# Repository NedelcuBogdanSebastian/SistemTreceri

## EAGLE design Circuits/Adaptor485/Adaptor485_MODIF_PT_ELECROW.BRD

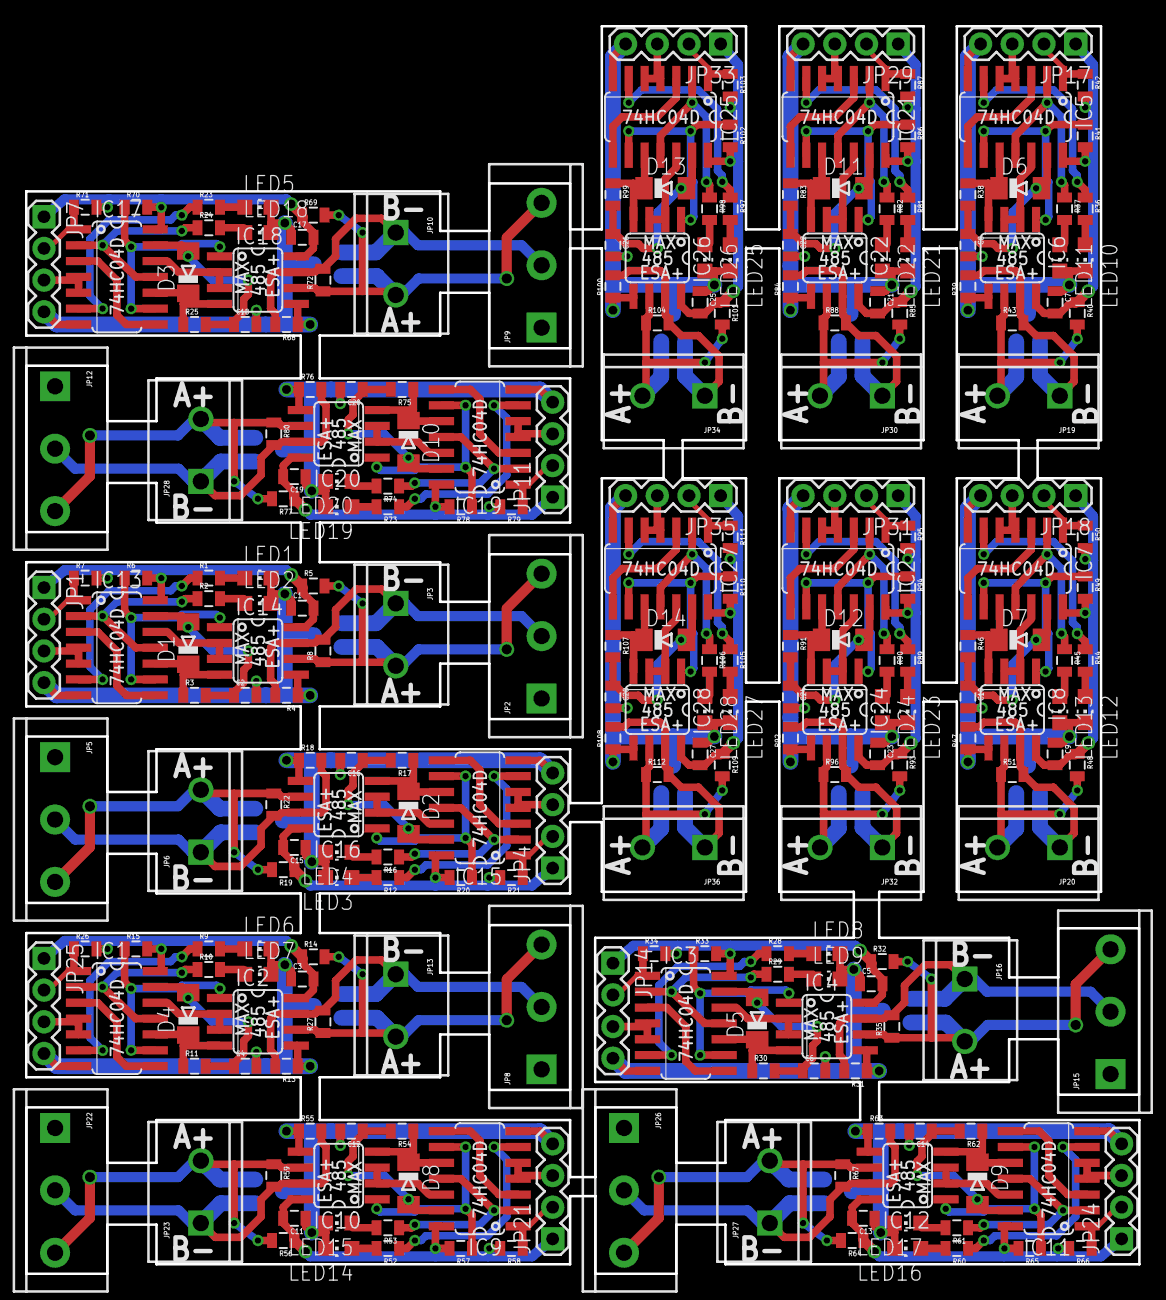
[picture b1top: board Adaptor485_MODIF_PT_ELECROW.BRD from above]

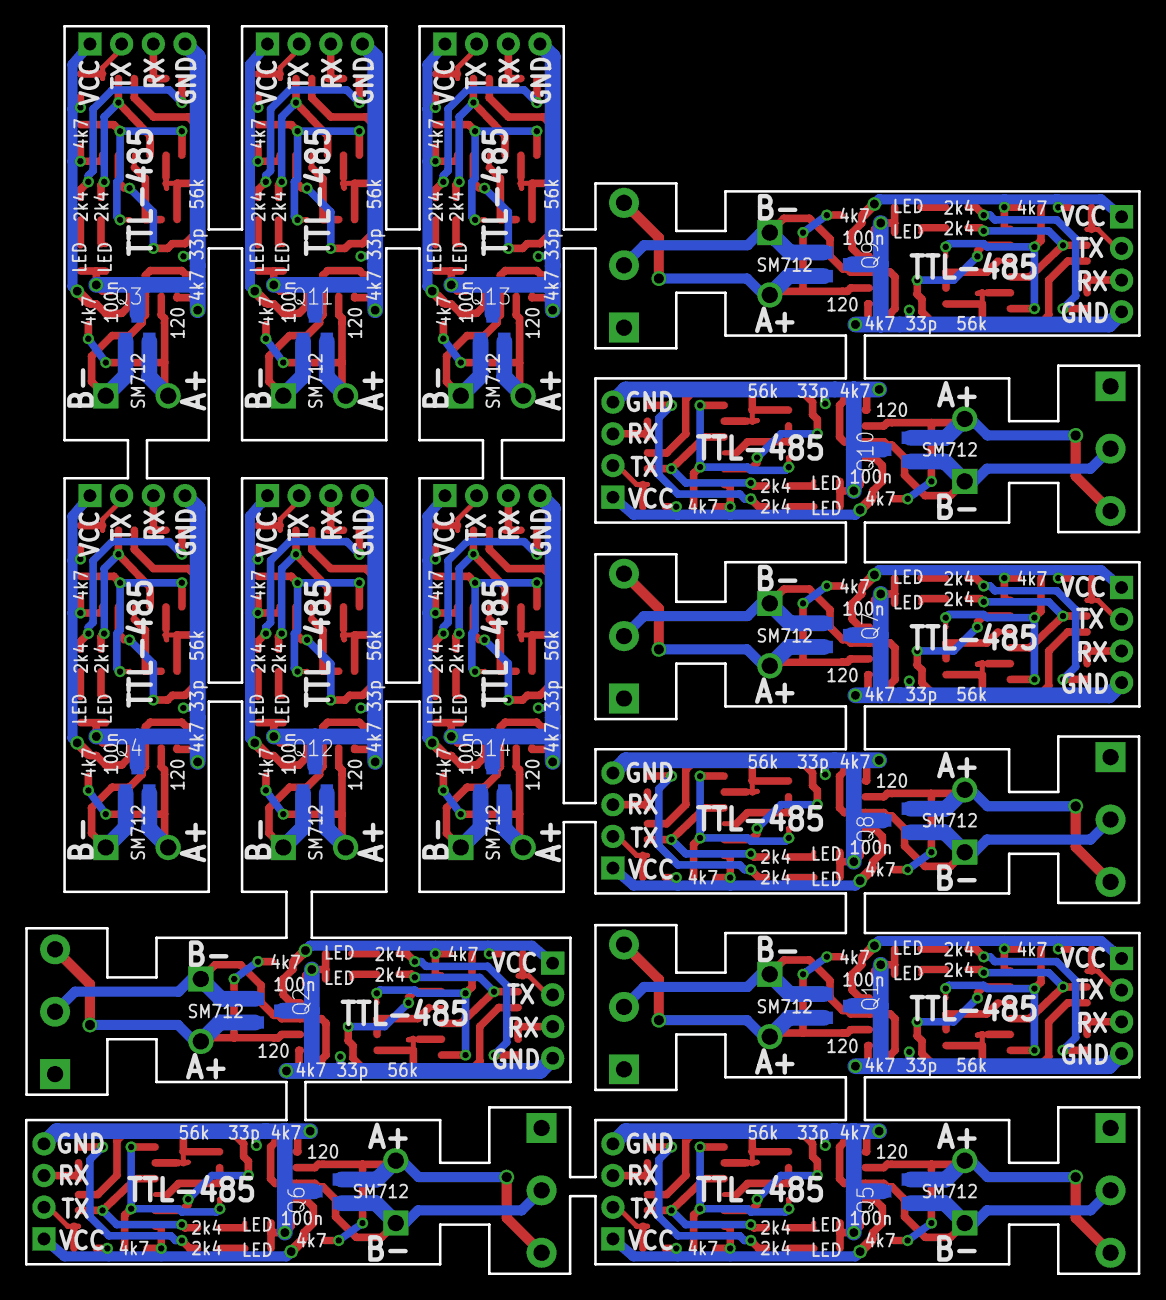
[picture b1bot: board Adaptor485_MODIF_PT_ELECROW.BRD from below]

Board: 2 copper layers, 89.2 x 100.0 mm, 260 parts (14 on the bottom side), 210 nets.

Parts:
C1, C3, C5, C7, C9, C11, C13, C15, C17, C19, C21, C23, C25, C27: 100n; 0805
C2, C4, C6, C8, C10, C12, C14, C16, C18, C20, C22, C24, C26, C28: 33pF; 0805
D1, D2, D3, D4, D5, D6, D7, D8, D9, D10, D11, D12, D13, D14: 1N4148; MINIMELF
IC1, IC3, IC5, IC7, IC9, IC11, IC13, IC15, IC17, IC19, IC21, IC23, IC25, IC27: 74HC04D; SO14
IC2, IC4, IC6, IC8, IC10, IC12, IC14, IC16, IC18, IC20, IC22, IC24, IC26, IC28: MAX3468CSA; SO08
JP1, JP4, JP7, JP11, JP14, JP17, JP18, JP21, JP24, JP25, JP29, JP31, JP33, JP35: 1X04
JP2, JP5, JP8, JP9, JP12, JP15, JP22, JP26: SCREWTERMINAL-5MM-3
JP3, JP6, JP10, JP13, JP16, JP19, JP20, JP23, JP27, JP28, JP30, JP32, JP34, JP36: SCREWTERMINAL-5MM-2
LED1, LED2, LED3, LED4, LED5, LED6, LED7, LED8, LED9, LED10, LED11, LED12, LED13, LED14, LED15, LED16, LED17, LED18, LED19, LED20, LED21, LED22, LED23, LED24, LED25, LED26, LED27, LED28: CHIP-LED0805
Q1, Q2, Q3, Q4, Q5, Q6, Q7, Q8, Q9, Q10, Q11, Q12, Q13, Q14: BCX70SMD; SOT23
R1, R2, R9, R10, R12, R16, R23, R24, R28, R29, R36, R37, R44, R45, R52, R53, R60, R61, R73, R74, R81, R82, R89, R90, R97, R98, R105, R106: 2K4; 0805
R3, R11, R17, R25, R30, R38, R46, R54, R62, R75, R83, R91, R99, R107: 56K; 0805
R4, R5, R6, R7, R13, R14, R15, R18, R19, R20, R21, R26, R31, R32, R33, R34, R39, R40, R41, R42, R47, R48, R49, R50, R55, R56, R57, R58, R63, R64, R65, R66, R68, R69, R70, R71, R76, R77, R78, R79, R84, R85, R86, R87, R92, R93, R94, R95, R100, R101, R102, R103, R108, R109, R110, R111: 4K7; 0805
R8, R22, R27, R35, R43, R51, R59, R67, R72, R80, R88, R96, R104, R112: 120; 0805

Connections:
3.3V1: C5.2, IC3.14, IC4.8, JP14.1, R32.1, R33.2, R34.2
3.3V2: C7.2, IC5.14, IC6.8, JP17.1, R40.1, R41.2, R42.2
3.3V3: C9.2, IC7.14, IC8.8, JP18.1, R48.1, R49.2, R50.2
3.3V4: C11.2, IC9.14, IC10.8, JP21.1, R56.1, R57.2, R58.2
3.3V5: C13.2, IC11.14, IC12.8, JP24.1, R64.1, R65.2, R66.2
3.3V6: C15.2, IC15.14, IC16.8, JP4.1, R19.1, R20.2, R21.2
3.3V7: C19.2, IC19.14, IC20.8, JP11.1, R77.1, R78.2, R79.2
3.3V8: C21.2, IC21.14, IC22.8, JP29.1, R85.1, R86.2, R87.2
3.3V9: C23.2, IC23.14, IC24.8, JP31.1, R93.1, R94.2, R95.2
3.3V10: C25.2, IC25.14, IC26.8, JP33.1, R101.1, R102.2, R103.2
3.3V11: C27.2, IC27.14, IC28.8, JP35.1, R109.1, R110.2, R111.2
A+: IC2.6, JP8.3, JP13.2, Q1.2, R14.2, R27.1
A+1: IC4.6, JP15.3, JP16.2, Q2.2, R32.2, R35.1
A+2: IC6.6, JP19.2, Q3.2, R40.2, R43.1
A+3: IC8.6, JP20.2, Q4.2, R48.2, R51.1
A+4: IC10.6, JP22.3, JP23.2, Q5.2, R56.2, R59.1
A+5: IC12.6, JP26.3, JP27.2, Q6.2, R64.2, R67.1
A+6: IC14.6, JP2.3, JP3.2, Q7.2, R5.2, R8.1
A+7: IC16.6, JP5.3, JP6.2, Q8.2, R19.2, R22.1
A+8: IC18.6, JP9.3, JP10.2, Q9.2, R69.2, R72.1
A+9: IC20.6, JP12.3, JP28.2, Q10.2, R77.2, R80.1
A+10: IC22.6, JP30.2, Q11.2, R85.2, R88.1
A+11: IC24.6, JP32.2, Q12.2, R93.2, R96.1
A+12: IC26.6, JP34.2, Q13.2, R101.2, R104.1
A+13: IC28.6, JP36.2, Q14.2, R109.2, R112.1
B-: IC2.7, JP8.2, JP13.1, Q1.1, R13.2, R27.2
B-1: IC4.7, JP15.2, JP16.1, Q2.1, R31.2, R35.2
B-2: IC6.7, JP19.1, Q3.1, R39.2, R43.2
B-3: IC8.7, JP20.1, Q4.1, R47.2, R51.2
B-4: IC10.7, JP22.2, JP23.1, Q5.1, R55.2, R59.2
B-5: IC12.7, JP26.2, JP27.1, Q6.1, R63.2, R67.2
B-6: IC14.7, JP2.2, JP3.1, Q7.1, R4.2, R8.2
B-7: IC16.7, JP5.2, JP6.1, Q8.1, R18.2, R22.2
B-8: IC18.7, JP9.2, JP10.1, Q9.1, R68.2, R72.2
B-9: IC20.7, JP12.2, JP28.1, Q10.1, R76.2, R80.2
B-10: IC22.7, JP30.1, Q11.1, R84.2, R88.2
B-11: IC24.7, JP32.1, Q12.1, R92.2, R96.2
B-12: IC26.7, JP34.1, Q13.1, R100.2, R104.2
B-13: IC28.7, JP36.1, Q14.1, R108.2, R112.2
GND: C3.1, C4.2, IC1.7, IC2.5, JP25.4, LED6.C, LED7.C, Q1.3, R13.1
GND2: C5.1, C6.2, IC3.7, IC4.5, JP14.4, LED8.C, LED9.C, Q2.3, R31.1
GND3: C7.1, C8.2, IC5.7, IC6.5, JP17.4, LED10.C, LED11.C, Q3.3, R39.1
GND4: C9.1, C10.2, IC7.7, IC8.5, JP18.4, LED12.C, LED13.C, Q4.3, R47.1
GND5: C11.1, C12.2, IC9.7, IC10.5, JP21.4, LED14.C, LED15.C, Q5.3, R55.1
GND6: C13.1, C14.2, IC11.7, IC12.5, JP24.4, LED16.C, LED17.C, Q6.3, R63.1
GND7: C1.1, C2.2, IC13.7, IC14.5, JP1.4, LED1.C, LED2.C, Q7.3, R4.1
GND8: C15.1, C16.2, IC15.7, IC16.5, JP4.4, LED3.C, LED4.C, Q8.3, R18.1
GND9: C17.1, C18.2, IC17.7, IC18.5, JP7.4, LED5.C, LED18.C, Q9.3, R68.1
GND10: C19.1, C20.2, IC19.7, IC20.5, JP11.4, LED19.C, LED20.C, Q10.3, R76.1
GND11: C21.1, C22.2, IC21.7, IC22.5, JP29.4, LED21.C, LED22.C, Q11.3, R84.1
GND12: C23.1, C24.2, IC23.7, IC24.5, JP31.4, LED23.C, LED24.C, Q12.3, R92.1
GND13: C25.1, C26.2, IC25.7, IC26.5, JP33.4, LED25.C, LED26.C, Q13.3, R100.1
GND14: C27.1, C28.2, IC27.7, IC28.5, JP35.4, LED27.C, LED28.C, Q14.3, R108.1
unnamed: IC13.9, IC14.1, R6.1
unnamed: IC13.3, IC13.8
unnamed: C2.1, D1.A, IC13.13, R3.2
unnamed: IC13.6, R1.1
unnamed: D1.C, IC13.10, IC14.4, R3.1
unnamed: IC13.12, IC14.2, IC14.3
unnamed: LED2.A, R2.2
unnamed: LED1.A, R1.2
unnamed: IC13.2, IC13.11, R2.1
unnamed: IC15.9, IC16.1, R20.1
unnamed: IC15.3, IC15.8
unnamed: C16.1, D2.A, IC15.13, R17.2
unnamed: IC3.9, IC4.1, R33.1
unnamed: IC3.3, IC3.8
unnamed: C6.1, D5.A, IC3.13, R30.2
unnamed: LED7.A, R10.2
unnamed: LED6.A, R9.2
unnamed: IC3.6, R28.1
unnamed: IC1.2, IC1.11, R10.1
unnamed: D5.C, IC3.10, IC4.4, R30.1
unnamed: IC1.9, IC2.1, R15.1
unnamed: IC15.6, R12.1
unnamed: IC1.3, IC1.8
unnamed: C4.1, D4.A, IC1.13, R11.2
unnamed: IC3.12, IC4.2, IC4.3
unnamed: LED9.A, R29.2
unnamed: IC1.6, R9.1
unnamed: LED8.A, R28.2
unnamed: D4.C, IC1.10, IC2.4, R11.1
unnamed: IC1.12, IC2.2, IC2.3
unnamed: IC3.2, IC3.11, R29.1
unnamed: IC5.9, IC6.1, R41.1
unnamed: IC5.3, IC5.8
unnamed: C8.1, D6.A, IC5.13, R38.2
unnamed: IC5.6, R36.1
unnamed: D6.C, IC5.10, IC6.4, R38.1
unnamed: IC5.12, IC6.2, IC6.3
unnamed: LED11.A, R37.2
unnamed: LED10.A, R36.2
unnamed: IC5.2, IC5.11, R37.1
unnamed: IC7.9, IC8.1, R49.1
unnamed: IC7.3, IC7.8
unnamed: C10.1, D7.A, IC7.13, R46.2
unnamed: IC7.6, R44.1
unnamed: D7.C, IC7.10, IC8.4, R46.1
unnamed: IC7.12, IC8.2, IC8.3
unnamed: LED13.A, R45.2
unnamed: LED12.A, R44.2
unnamed: IC7.2, IC7.11, R45.1
unnamed: IC9.9, IC10.1, R57.1
unnamed: IC9.3, IC9.8
unnamed: C12.1, D8.A, IC9.13, R54.2
unnamed: D2.C, IC15.10, IC16.4, R17.1
unnamed: IC15.12, IC16.2, IC16.3
unnamed: LED4.A, R16.2
unnamed: LED3.A, R12.2
unnamed: IC15.2, IC15.11, R16.1
unnamed: IC17.9, IC18.1, R70.1
unnamed: IC17.3, IC17.8
unnamed: C18.1, D3.A, IC17.13, R25.2
unnamed: IC17.6, R23.1
unnamed: D3.C, IC17.10, IC18.4, R25.1
unnamed: IC9.6, R52.1
unnamed: D8.C, IC9.10, IC10.4, R54.1
unnamed: IC9.12, IC10.2, IC10.3
unnamed: LED15.A, R53.2
unnamed: LED14.A, R52.2
unnamed: IC9.2, IC9.11, R53.1
unnamed: IC11.9, IC12.1, R65.1
unnamed: IC11.3, IC11.8
unnamed: C14.1, D9.A, IC11.13, R62.2
unnamed: IC11.6, R60.1
unnamed: D9.C, IC11.10, IC12.4, R62.1
unnamed: IC11.12, IC12.2, IC12.3
unnamed: LED17.A, R61.2
unnamed: LED16.A, R60.2
unnamed: IC17.12, IC18.2, IC18.3
unnamed: LED18.A, R24.2
unnamed: IC11.2, IC11.11, R61.1
unnamed: LED5.A, R23.2
unnamed: IC17.2, IC17.11, R24.1
unnamed: IC19.9, IC20.1, R78.1
unnamed: IC19.3, IC19.8
unnamed: C20.1, D10.A, IC19.13, R75.2
unnamed: IC19.6, R73.1
unnamed: D10.C, IC19.10, IC20.4, R75.1
unnamed: IC19.12, IC20.2, IC20.3
unnamed: LED20.A, R74.2
unnamed: LED19.A, R73.2
unnamed: IC19.2, IC19.11, R74.1
unnamed: IC21.9, IC22.1, R86.1
unnamed: IC21.3, IC21.8
unnamed: C22.1, D11.A, IC21.13, R83.2
unnamed: IC21.6, R81.1
unnamed: D11.C, IC21.10, IC22.4, R83.1
unnamed: IC21.12, IC22.2, IC22.3
unnamed: LED22.A, R82.2
unnamed: LED21.A, R81.2
unnamed: IC21.2, IC21.11, R82.1
unnamed: IC23.9, IC24.1, R94.1
unnamed: IC23.3, IC23.8
unnamed: C24.1, D12.A, IC23.13, R91.2
unnamed: IC23.6, R89.1
unnamed: D12.C, IC23.10, IC24.4, R91.1
unnamed: IC23.12, IC24.2, IC24.3
unnamed: LED24.A, R90.2
unnamed: LED23.A, R89.2
unnamed: IC23.2, IC23.11, R90.1
unnamed: IC25.9, IC26.1, R102.1
unnamed: IC25.3, IC25.8
unnamed: C26.1, D13.A, IC25.13, R99.2
unnamed: IC25.6, R97.1
unnamed: D13.C, IC25.10, IC26.4, R99.1
unnamed: IC25.12, IC26.2, IC26.3
unnamed: LED26.A, R98.2
unnamed: LED25.A, R97.2
unnamed: IC25.2, IC25.11, R98.1
unnamed: IC27.9, IC28.1, R110.1
unnamed: IC27.3, IC27.8
unnamed: C28.1, D14.A, IC27.13, R107.2
unnamed: IC27.6, R105.1
unnamed: D14.C, IC27.10, IC28.4, R107.1
unnamed: IC27.12, IC28.2, IC28.3
unnamed: LED28.A, R106.2
unnamed: LED27.A, R105.2
unnamed: IC27.2, IC27.11, R106.1
RX: IC1.1, JP25.2, R26.1
RX1: IC3.1, JP14.2, R34.1
RX2: IC5.1, JP17.2, R42.1
RX3: IC7.1, JP18.2, R50.1
RX4: IC9.1, JP21.2, R58.1
RX5: IC11.1, JP24.2, R66.1
RX6: IC13.1, JP1.2, R7.1
RX7: IC15.1, JP4.2, R21.1
RX8: IC17.1, JP7.2, R71.1
RX9: IC19.1, JP11.2, R79.1
RX10: IC21.1, JP29.2, R87.1
RX11: IC23.1, JP31.2, R95.1
RX12: IC25.1, JP33.2, R103.1
RX13: IC27.1, JP35.2, R111.1
S$1: C3.2, IC1.14, IC2.8, JP25.1, R14.1, R15.2, R26.2
S$2: C1.2, IC13.14, IC14.8, JP1.1, R5.1, R6.2, R7.2
S$3: C17.2, IC17.14, IC18.8, JP7.1, R69.1, R70.2, R71.2
TX: IC1.4, IC1.5, JP25.3
TX1: IC3.4, IC3.5, JP14.3
TX2: IC5.4, IC5.5, JP17.3
TX3: IC7.4, IC7.5, JP18.3
TX4: IC9.4, IC9.5, JP21.3
TX5: IC11.4, IC11.5, JP24.3
TX6: IC13.4, IC13.5, JP1.3
TX7: IC15.4, IC15.5, JP4.3
TX8: IC17.4, IC17.5, JP7.3
TX9: IC19.4, IC19.5, JP11.3
TX10: IC21.4, IC21.5, JP29.3
TX11: IC23.4, IC23.5, JP31.3
TX12: IC25.4, IC25.5, JP33.3
TX13: IC27.4, IC27.5, JP35.3

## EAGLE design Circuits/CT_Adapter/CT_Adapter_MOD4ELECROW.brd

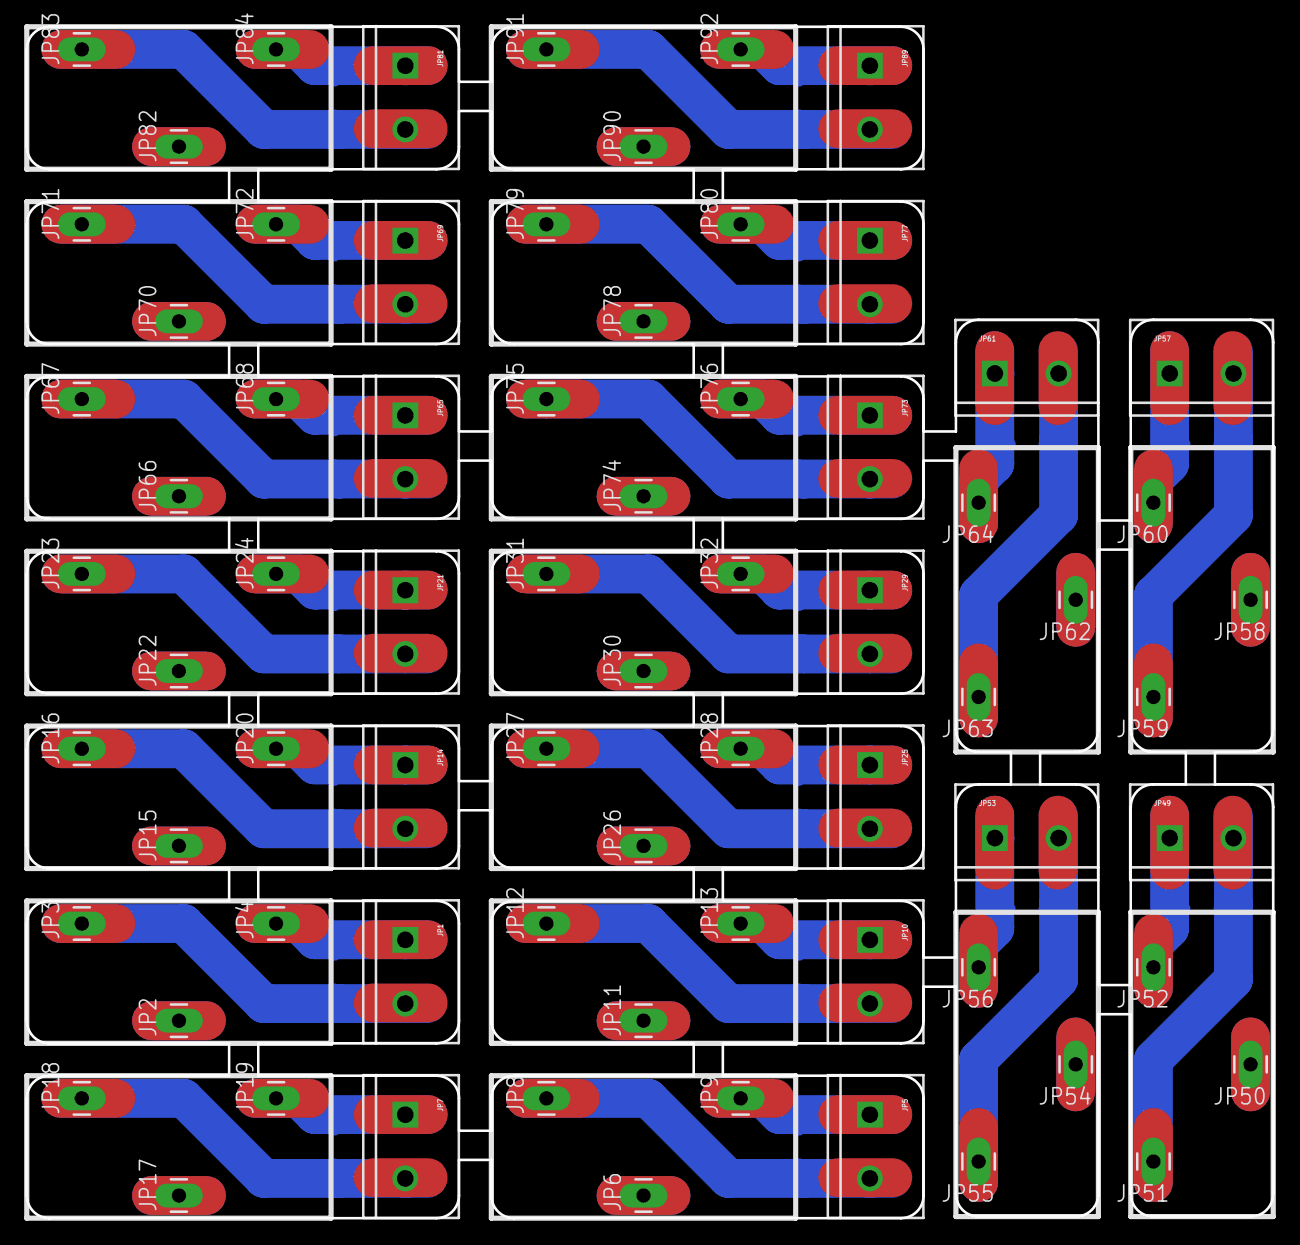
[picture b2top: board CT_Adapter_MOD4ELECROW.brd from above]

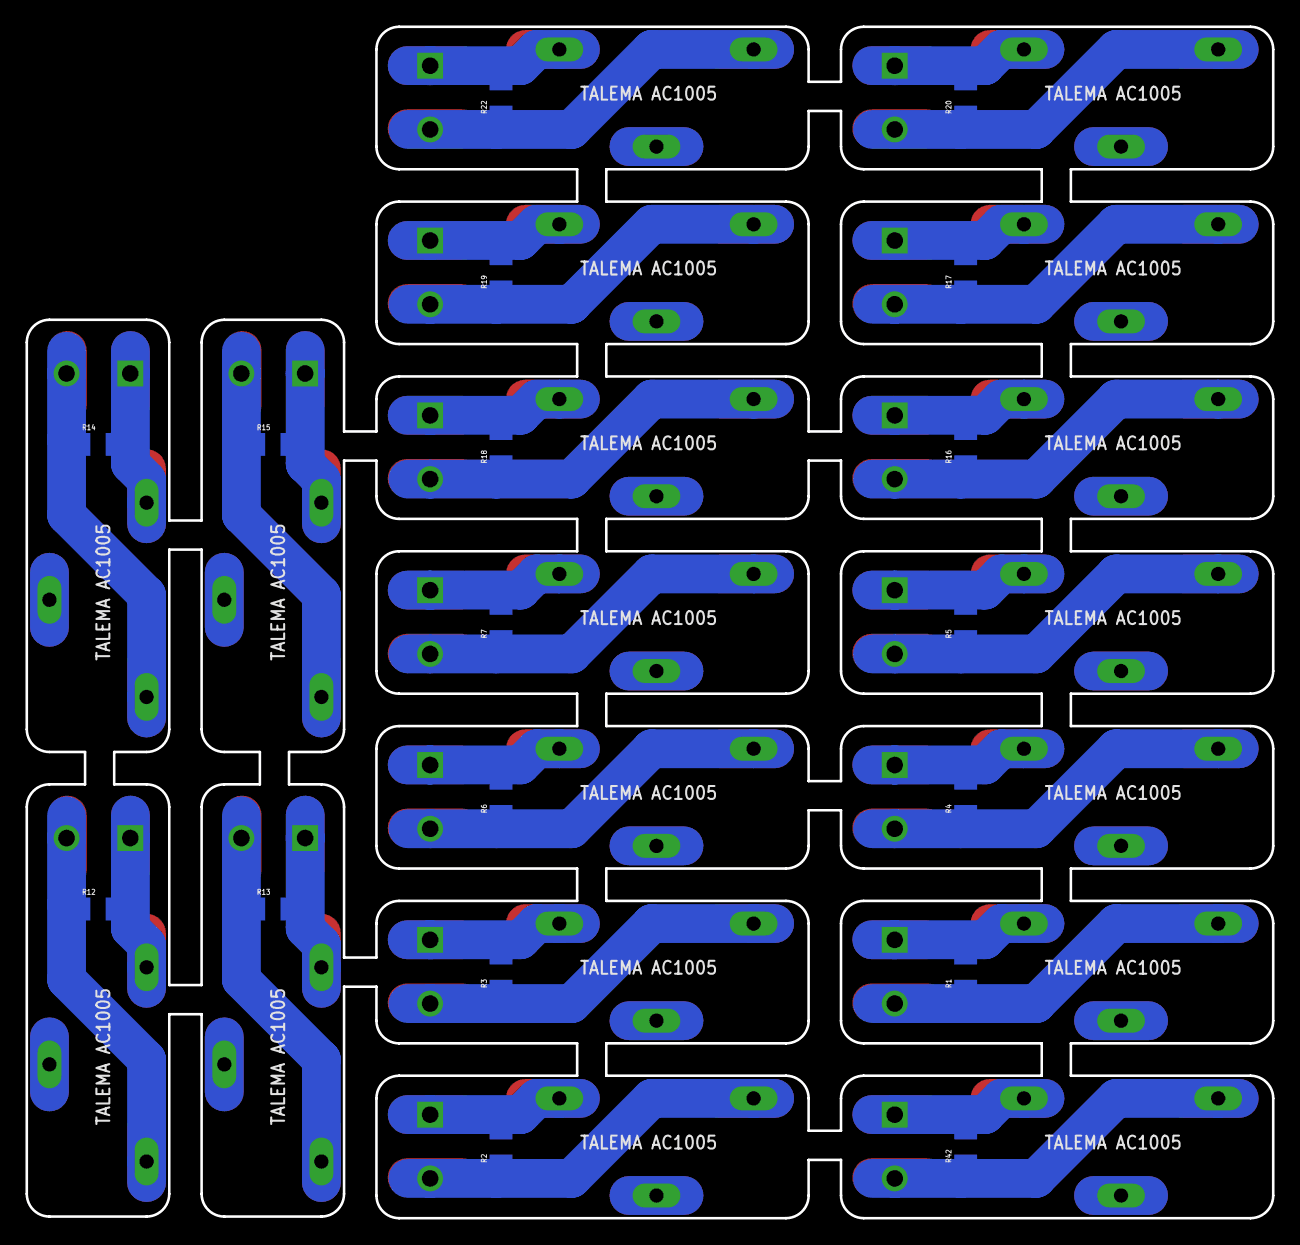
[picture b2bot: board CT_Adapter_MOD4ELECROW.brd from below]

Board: 2 copper layers, 97.8 x 93.5 mm, 90 parts (18 on the bottom side), 36 nets.

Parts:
JP1, JP5, JP7, JP10, JP14, JP21, JP25, JP29, JP49, JP53, JP57, JP61, JP65, JP69, JP73, JP77, JP81, JP89: SCREWTERMINAL-5MM-2
JP2, JP3, JP4, JP6, JP8, JP9, JP11, JP12, JP13, JP15, JP16, JP17, JP18, JP19, JP20, JP22, JP23, JP24, JP26, JP27, JP28, JP30, JP31, JP32, JP50, JP51, JP52, JP54, JP55, JP56, JP58, JP59, JP60, JP62, JP63, JP64, JP66, JP67, JP68, JP70, JP71, JP72, JP74, JP75, JP76, JP78, JP79, JP80, JP82, JP83, JP84, JP90, JP91, JP92: 1X01_LONGPAD
R1, R2, R3, R4, R5, R6, R7, R12, R13, R14, R15, R16, R17, R18, R19, R20, R22, R42: 50ohm; 1206

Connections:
AGND: JP7.1, JP19.1, R42.2
AGND1: JP1.1, JP4.1, R1.2
AGND2: JP5.1, JP9.1, R2.2
AGND3: JP10.1, JP13.1, R3.2
AGND4: JP14.1, JP20.1, R4.2
AGND5: JP21.1, JP24.1, R5.2
AGND6: JP25.1, JP28.1, R6.2
AGND7: JP29.1, JP32.1, R7.2
AGND12: JP49.1, JP52.1, R12.2
AGND13: JP53.1, JP56.1, R13.2
AGND14: JP57.1, JP60.1, R14.2
AGND15: JP61.1, JP64.1, R15.2
AGND16: JP65.1, JP68.1, R16.2
AGND17: JP69.1, JP72.1, R17.2
AGND18: JP73.1, JP76.1, R18.2
AGND19: JP77.1, JP80.1, R19.2
AGND20: JP81.1, JP84.1, R20.2
AGND22: JP89.1, JP92.1, R22.2
unnamed: JP7.2, JP18.1, R42.1
unnamed: JP1.2, JP3.1, R1.1
unnamed: JP5.2, JP8.1, R2.1
unnamed: JP10.2, JP12.1, R3.1
unnamed: JP14.2, JP16.1, R4.1
unnamed: JP21.2, JP23.1, R5.1
unnamed: JP25.2, JP27.1, R6.1
unnamed: JP29.2, JP31.1, R7.1
unnamed: JP49.2, JP51.1, R12.1
unnamed: JP53.2, JP55.1, R13.1
unnamed: JP57.2, JP59.1, R14.1
unnamed: JP61.2, JP63.1, R15.1
unnamed: JP65.2, JP67.1, R16.1
unnamed: JP69.2, JP71.1, R17.1
unnamed: JP73.2, JP75.1, R18.1
unnamed: JP77.2, JP79.1, R19.1
unnamed: JP81.2, JP83.1, R20.1
unnamed: JP89.2, JP91.1, R22.1

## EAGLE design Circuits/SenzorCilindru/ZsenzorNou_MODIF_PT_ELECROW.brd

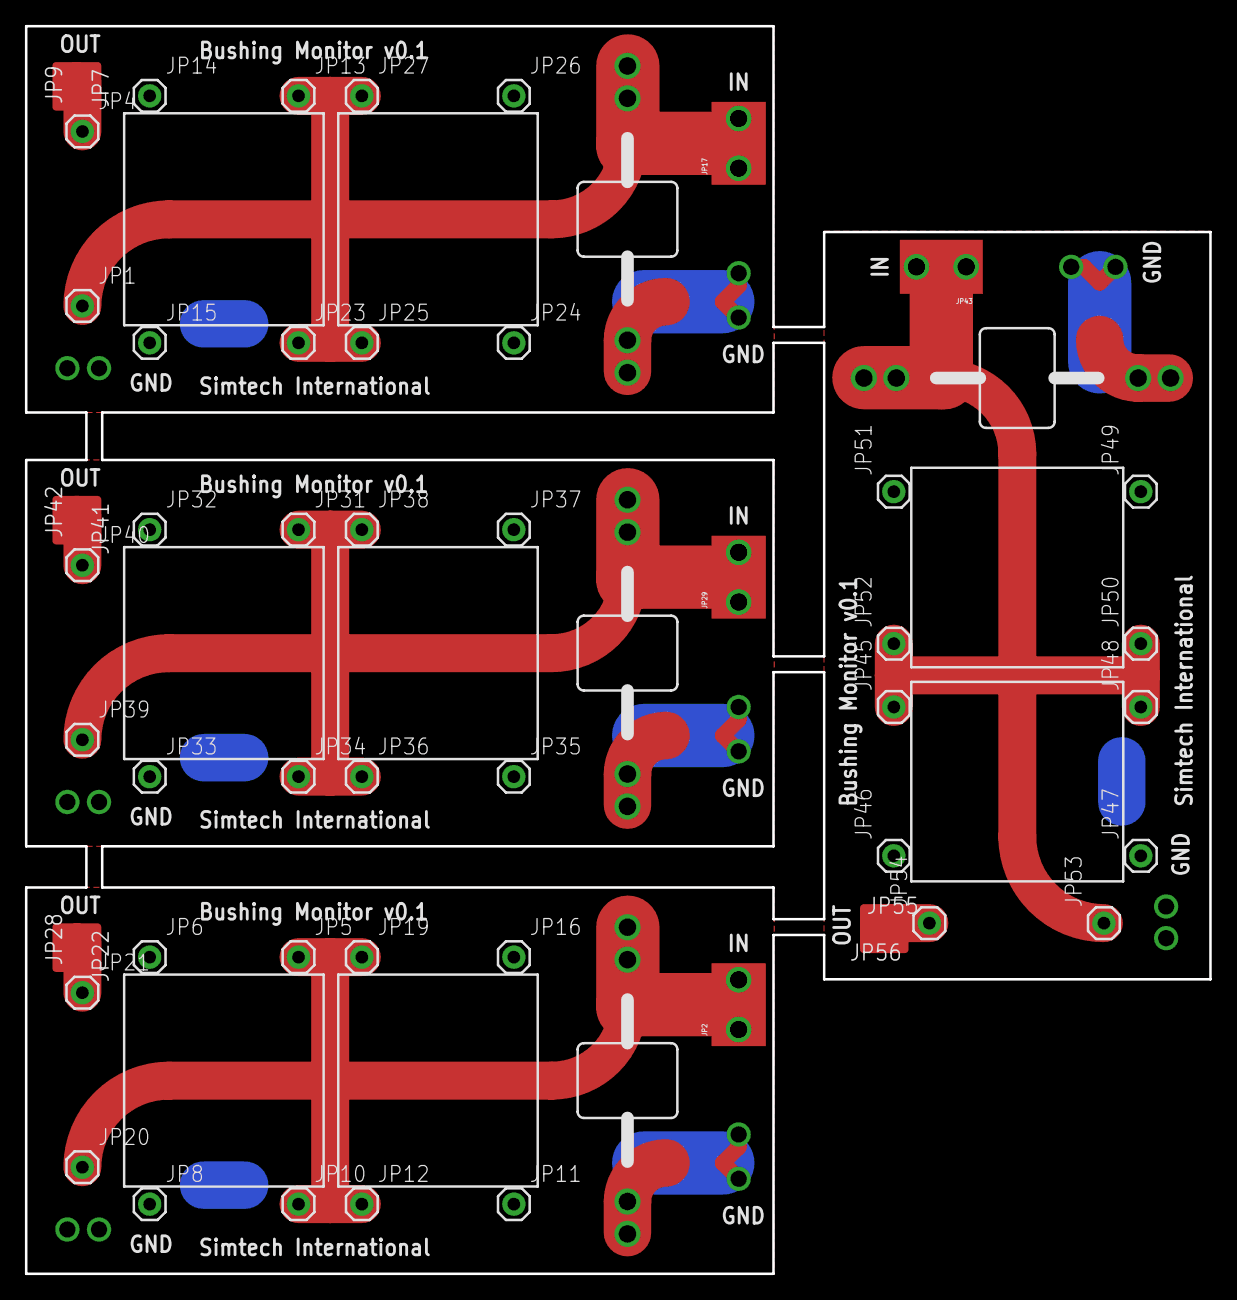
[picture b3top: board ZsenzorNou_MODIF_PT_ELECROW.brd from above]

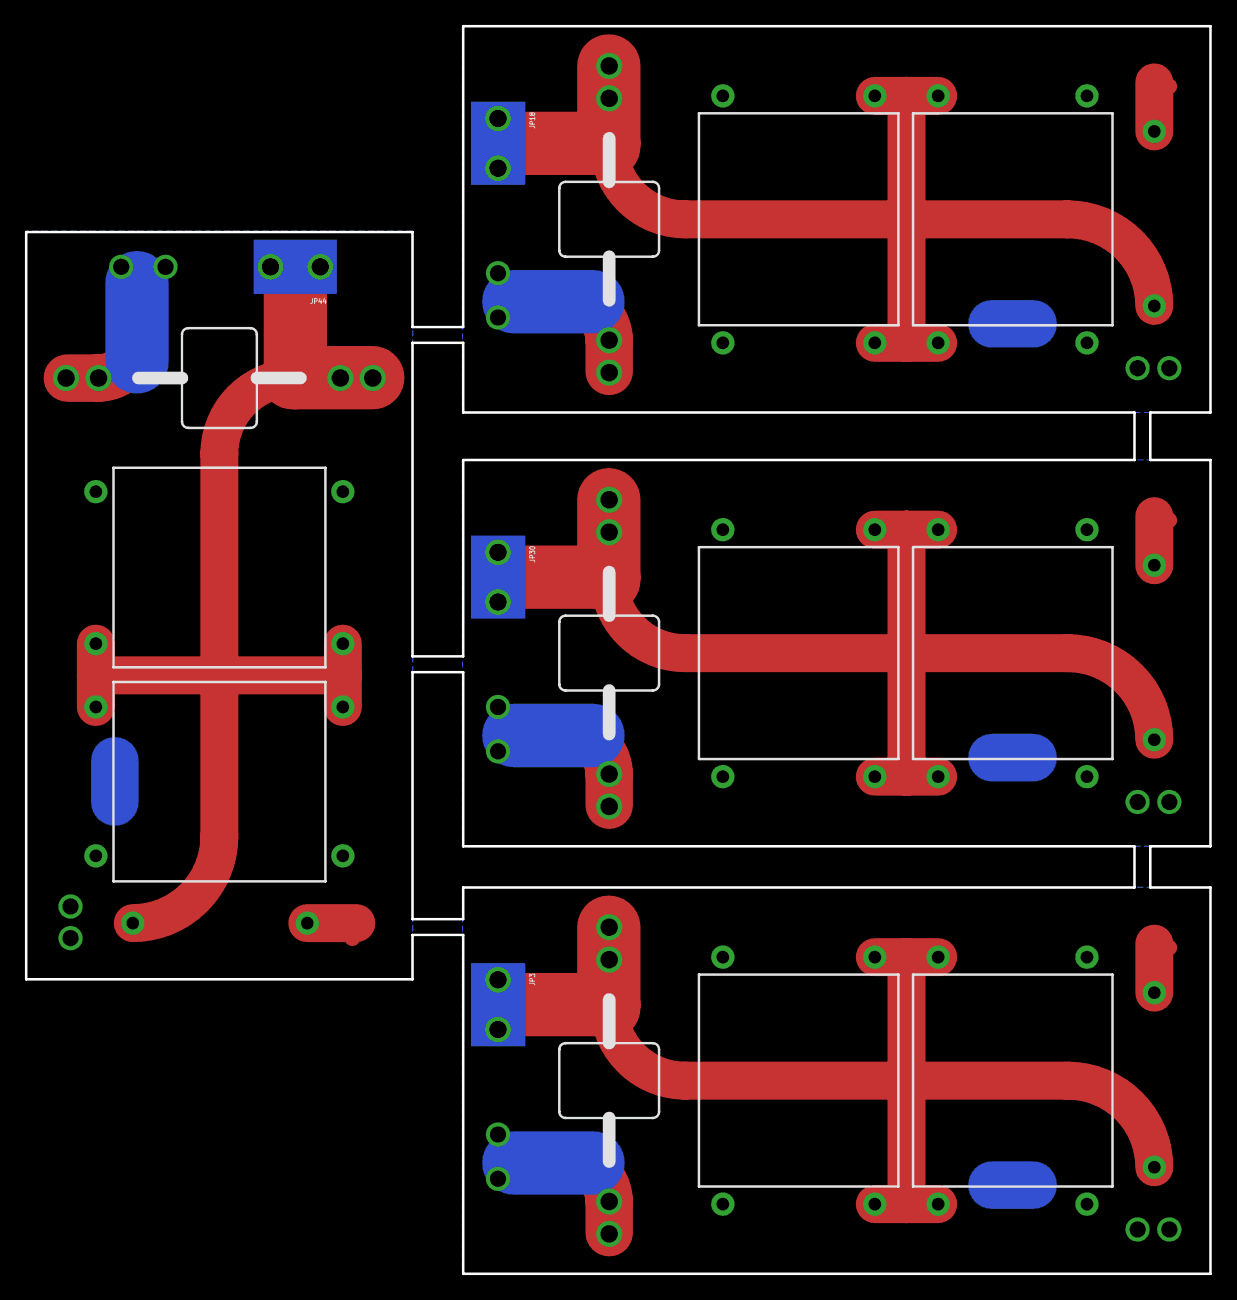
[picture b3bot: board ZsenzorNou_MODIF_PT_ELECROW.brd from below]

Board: 2 copper layers, 95.0 x 100.1 mm, 56 parts (4 on the bottom side), 8 nets.

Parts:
JP1, JP4, JP5, JP6, JP8, JP10, JP11, JP12, JP13, JP14, JP15, JP16, JP19, JP20, JP21, JP23, JP24, JP25, JP26, JP27, JP31, JP32, JP33, JP34, JP35, JP36, JP37, JP38, JP39, JP40, JP45, JP46, JP47, JP48, JP49, JP50, JP51, JP52, JP53, JP54: M01PTH; 1X01
JP2, JP3, JP17, JP18, JP29, JP30, JP43, JP44: M01SMTRA-256-8-6; SMTRA-256-8-6
JP7, JP9, JP22, JP28, JP41, JP42, JP55, JP56: M01SMD; LUXEON-PAD

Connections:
GND: JP14.1, JP15.1, JP24.1, JP26.1
GND1: JP6.1, JP8.1, JP11.1, JP16.1
GND2: JP32.1, JP33.1, JP35.1, JP37.1
GND3: JP46.1, JP47.1, JP49.1, JP51.1
unnamed: JP2.P$1, JP3.P$1, JP5.1, JP10.1, JP12.1, JP19.1, JP20.1, JP21.1, JP22.P$1, JP28.P$1
unnamed: JP29.P$1, JP30.P$1, JP31.1, JP34.1, JP36.1, JP38.1, JP39.1, JP40.1, JP41.P$1, JP42.P$1
unnamed: JP1.1, JP4.1, JP7.P$1, JP9.P$1, JP13.1, JP17.P$1, JP18.P$1, JP23.1, JP25.1, JP27.1
unnamed: JP43.P$1, JP44.P$1, JP45.1, JP48.1, JP50.1, JP52.1, JP53.1, JP54.1, JP55.P$1, JP56.P$1

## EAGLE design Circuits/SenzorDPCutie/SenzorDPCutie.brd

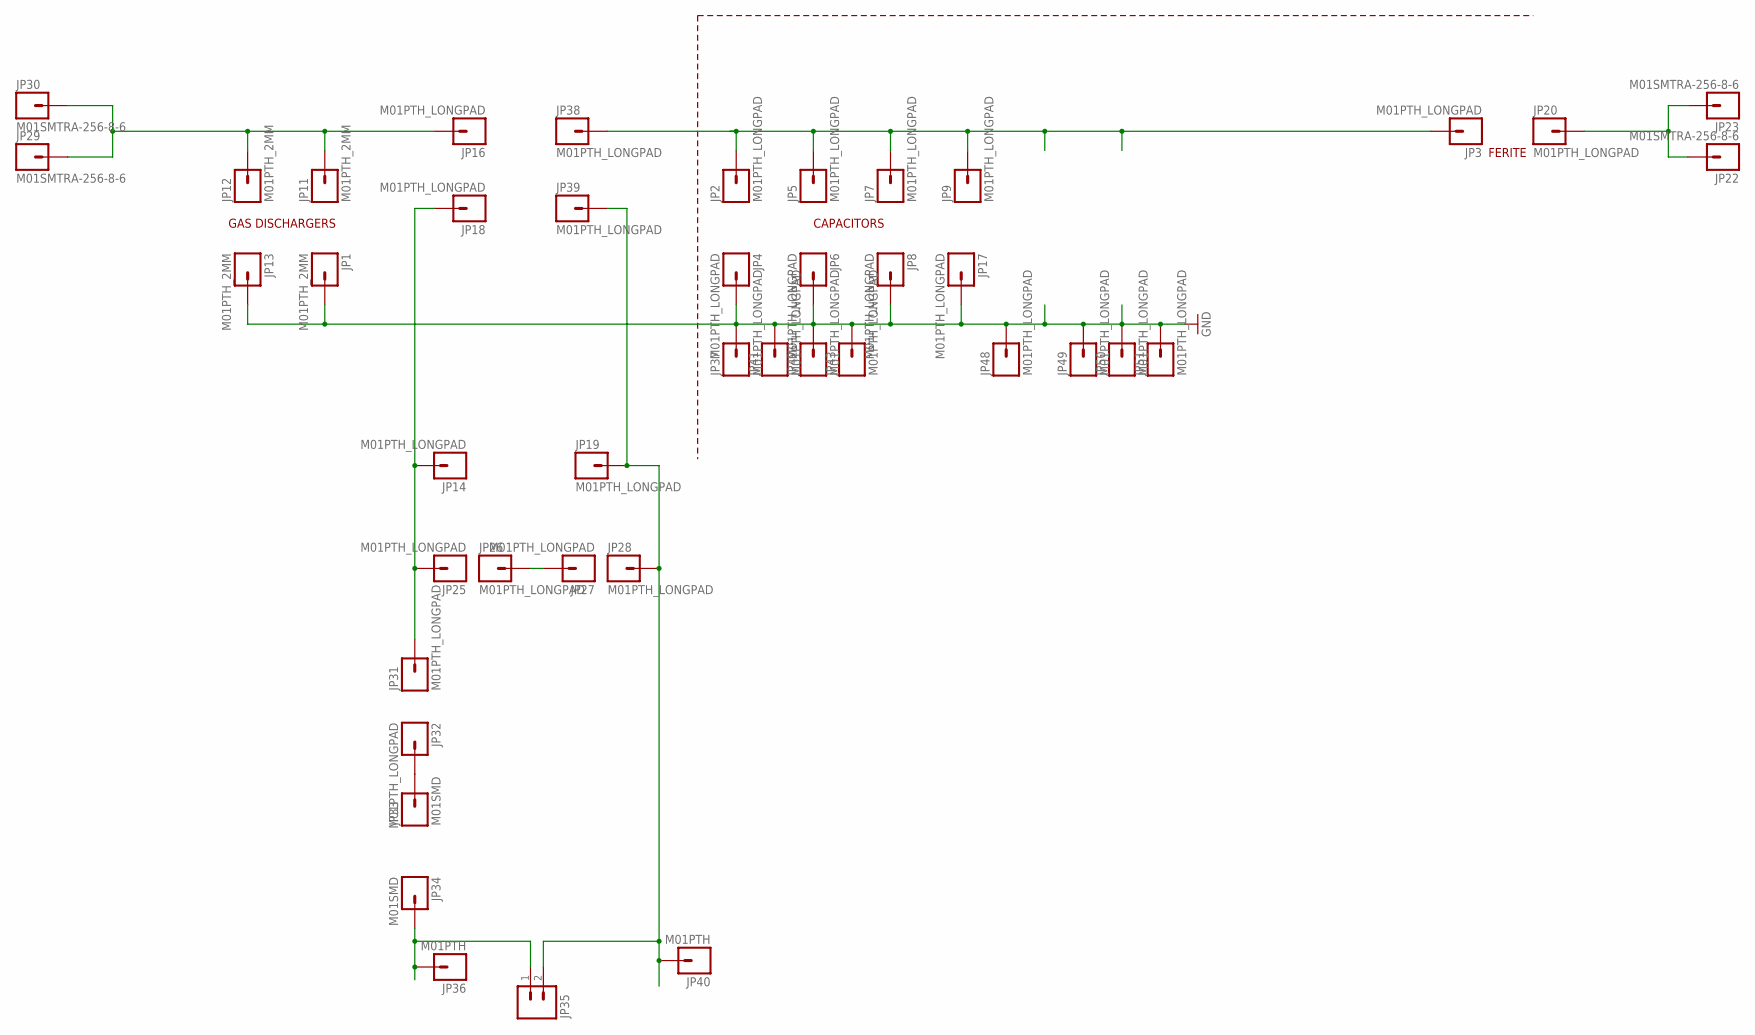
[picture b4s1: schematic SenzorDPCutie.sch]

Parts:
JP1, JP11, JP12, JP13: M01PTH_2MM; 1X01_2MM
JP2, JP3, JP4, JP5, JP6, JP7, JP8, JP9, JP14, JP16, JP17, JP18, JP19, JP20, JP25, JP26, JP27, JP28, JP31, JP32, JP37, JP38, JP39, JP41, JP42, JP43, JP48, JP49, JP50, JP51: M01PTH_LONGPAD; 1X01_LONGPAD
JP22, JP23, JP29, JP30: M01SMTRA-256-8-6; SMTRA-256-8-6
JP33, JP34: M01SMD; LUXEON-PAD
JP35: M025MM; SCREWTERMINAL-5MM-2
JP36, JP40: M01PTH; 1X01

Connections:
GND: JP1.1, JP4.1, JP6.1, JP8.1, JP13.1, JP17.1, JP37.1, JP41.1, JP42.1, JP43.1, JP48.1, JP49.1, JP50.1, JP51.1
unnamed: JP20.1, JP22.P$1, JP23.P$1
unnamed: JP26.1, JP27.1
unnamed: JP32.1, JP33.P$1
unnamed: JP34.P$1, JP35.1, JP36.1
unnamed: JP2.1, JP3.1, JP5.1, JP7.1, JP9.1, JP38.1
unnamed: JP14.1, JP18.1, JP25.1, JP31.1
unnamed: JP19.1, JP28.1, JP35.2, JP39.1, JP40.1
SIG: JP11.1, JP12.1, JP16.1, JP29.P$1, JP30.P$1

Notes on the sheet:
CAPACITORS
GAS DISCHARGERS
FERITE

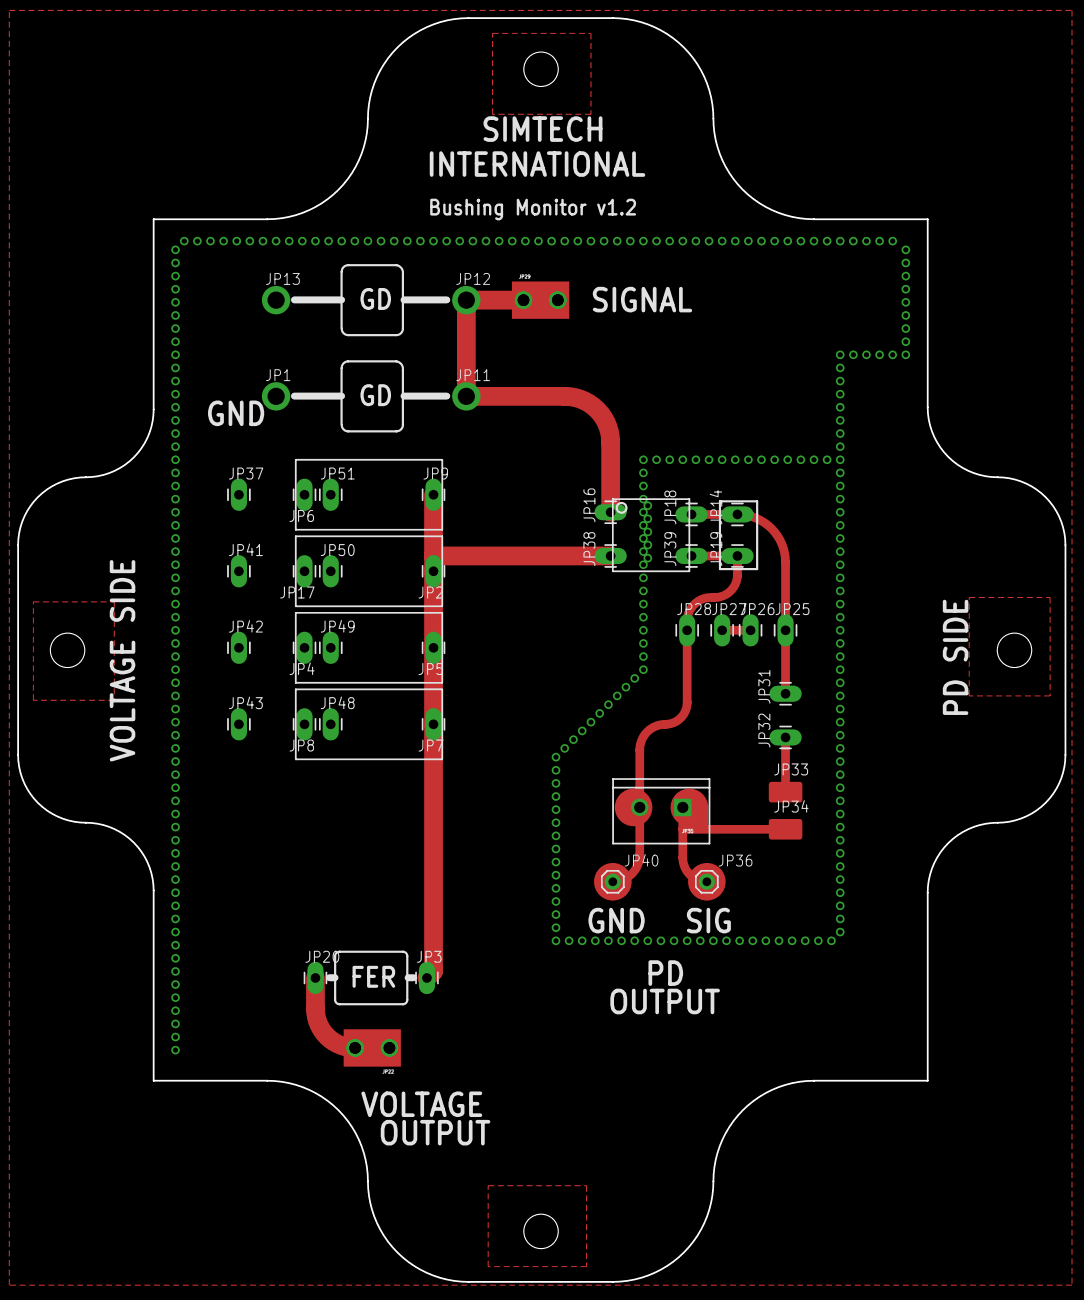
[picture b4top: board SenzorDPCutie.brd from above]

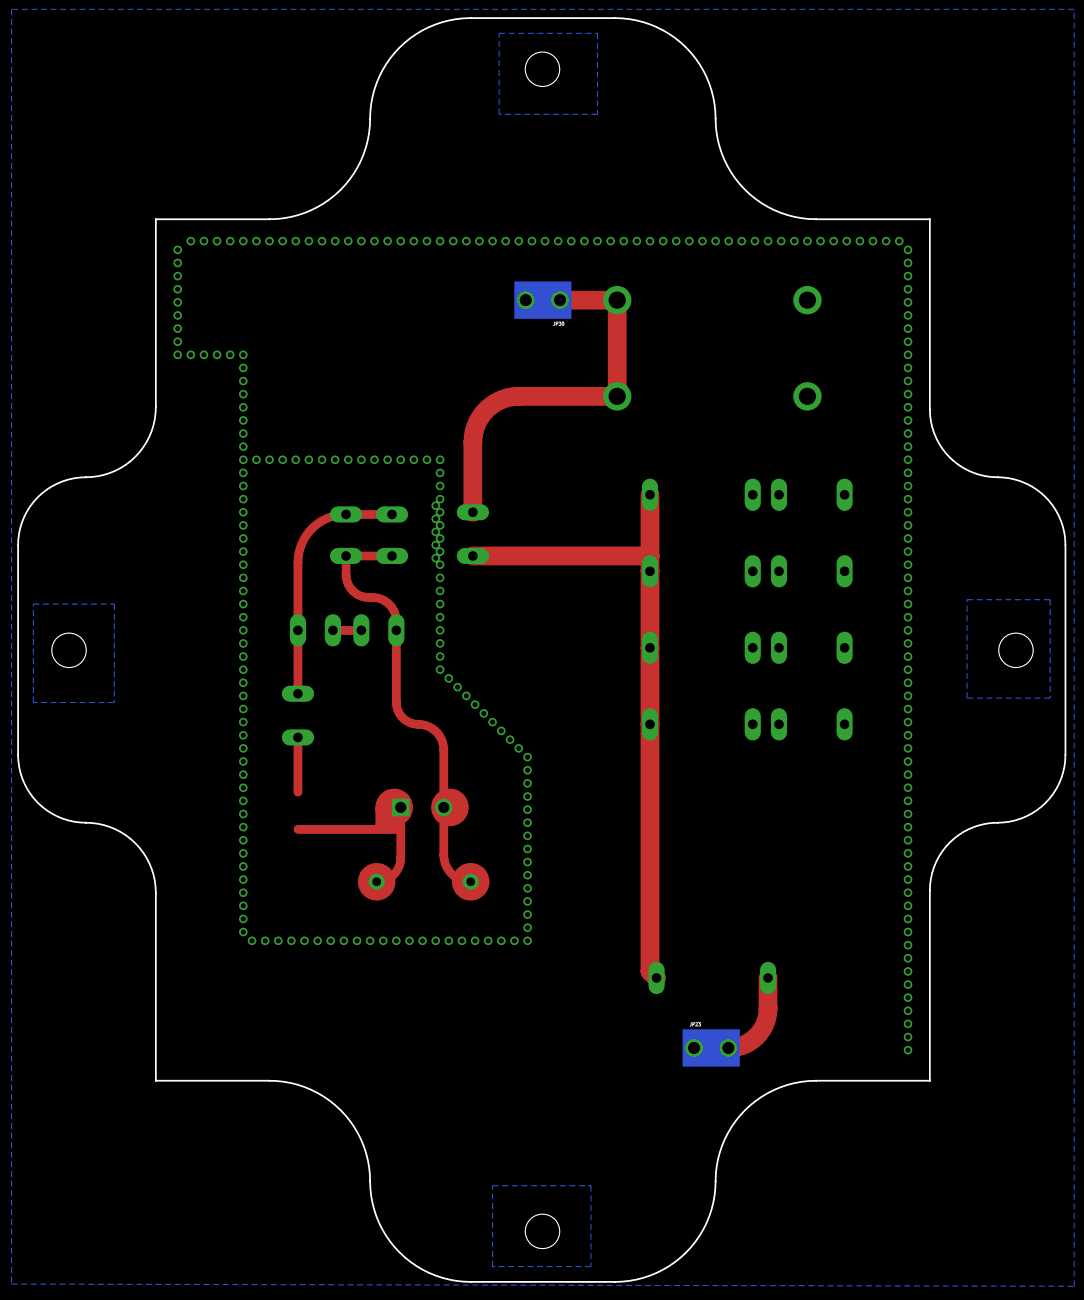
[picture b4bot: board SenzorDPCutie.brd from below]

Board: 2 copper layers, 121.7 x 146.8 mm, 43 parts (2 on the bottom side), 9 nets.

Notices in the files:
parts and their libraries:
SparkFun-Connectors: Licensing: CC v3.0 Share-Alike You are welcome to use this library for commercial purposes.
SparkFun-Passives: Licensing: Creative Commons ShareAlike 4.0 International - https://creativecommons.org/licenses/by-sa/4.0
